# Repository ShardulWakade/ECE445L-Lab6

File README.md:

# Lab 6 Introduction to PCB Design

## Table of Contents

- [Lab 6 Introduction to PCB Design](#lab-6-introduction-to-pcb-design)
  - [Table of Contents](#table-of-contents)
  - [0 Repository Structure](#0-repository-structure)
    - [0.1 HW](#01-hw)
    - [0.2 SW](#02-sw)
    - [0.3 Resources](#03-resources)
    - [0.4 Git and Github](#04-git-and-github)
---

## 0 Repository Structure

The typical explanation for the repo structure. Lab specific instructions can be
found further below.

### 0.1 HW

The `hw` folder should contain your schematic and board files for your PCB or
circuits. In labs 1-5 and 10, you will be creating schematics for your circuit
in EAGLE. A setup tutorial can be found
[here](https://www.shawnvictor.net/autodesk-eagle.html).

### 0.2 SW

The `sw` folder should contain your application firmware and software written
for the lab. The `sw/inc` folder contains firmware drivers written for you by
Professor Valvano. Feel free to write your own (in fact, in some labs, you may
be required to write your own).

You can place any other source files in the `sw` folder. TAs will look at the
files you create and/or modify for software quality and for running your
project.

### 0.3 Resources

A couple files are provided in the Resources folder so you don't have to keep
searching for that one TI document. Some of them are immediately useful, like
the TM4C datasheet. Others may be useful for your final project, like the
TM4C_System_Design_Guidelines page.

### 0.4 Git and Github

We will extensively use Git and Github for managing lab projects. This makes it
easier for TAs to grade and help debug the project by allowing us to see commit
histories, maintain a common project structure, and likewise, it makes it easier
for students to collaborate with partners, merge different codebases, and to
debug their work by having a history of commits.

Two common ways of using Git and Github are [Github Desktop](https://desktop.github.com/) and the [command line](https://git-scm.com/downloads).
[Tutorials](https://dev.to/mollynem/git-github--workflow-fundamentals-5496) are also abundant on the net for you to peruse. We've provided a cheatsheet for git
in the Resources folder.

It is highly recommended to make the most out of Git, even if you've never used
it before. Version control will save you a lot of suffering, and tools like Git
or SVN are ubiquitous in the industry.

A gitignore file is added to the root of this repo that may prevent specific
files from being tagged to the repo. This are typically autogenerated output
files we don't care about, but sometimes other stuff (like .lib files) falls
through that we want. Feel free to modify if necessary.

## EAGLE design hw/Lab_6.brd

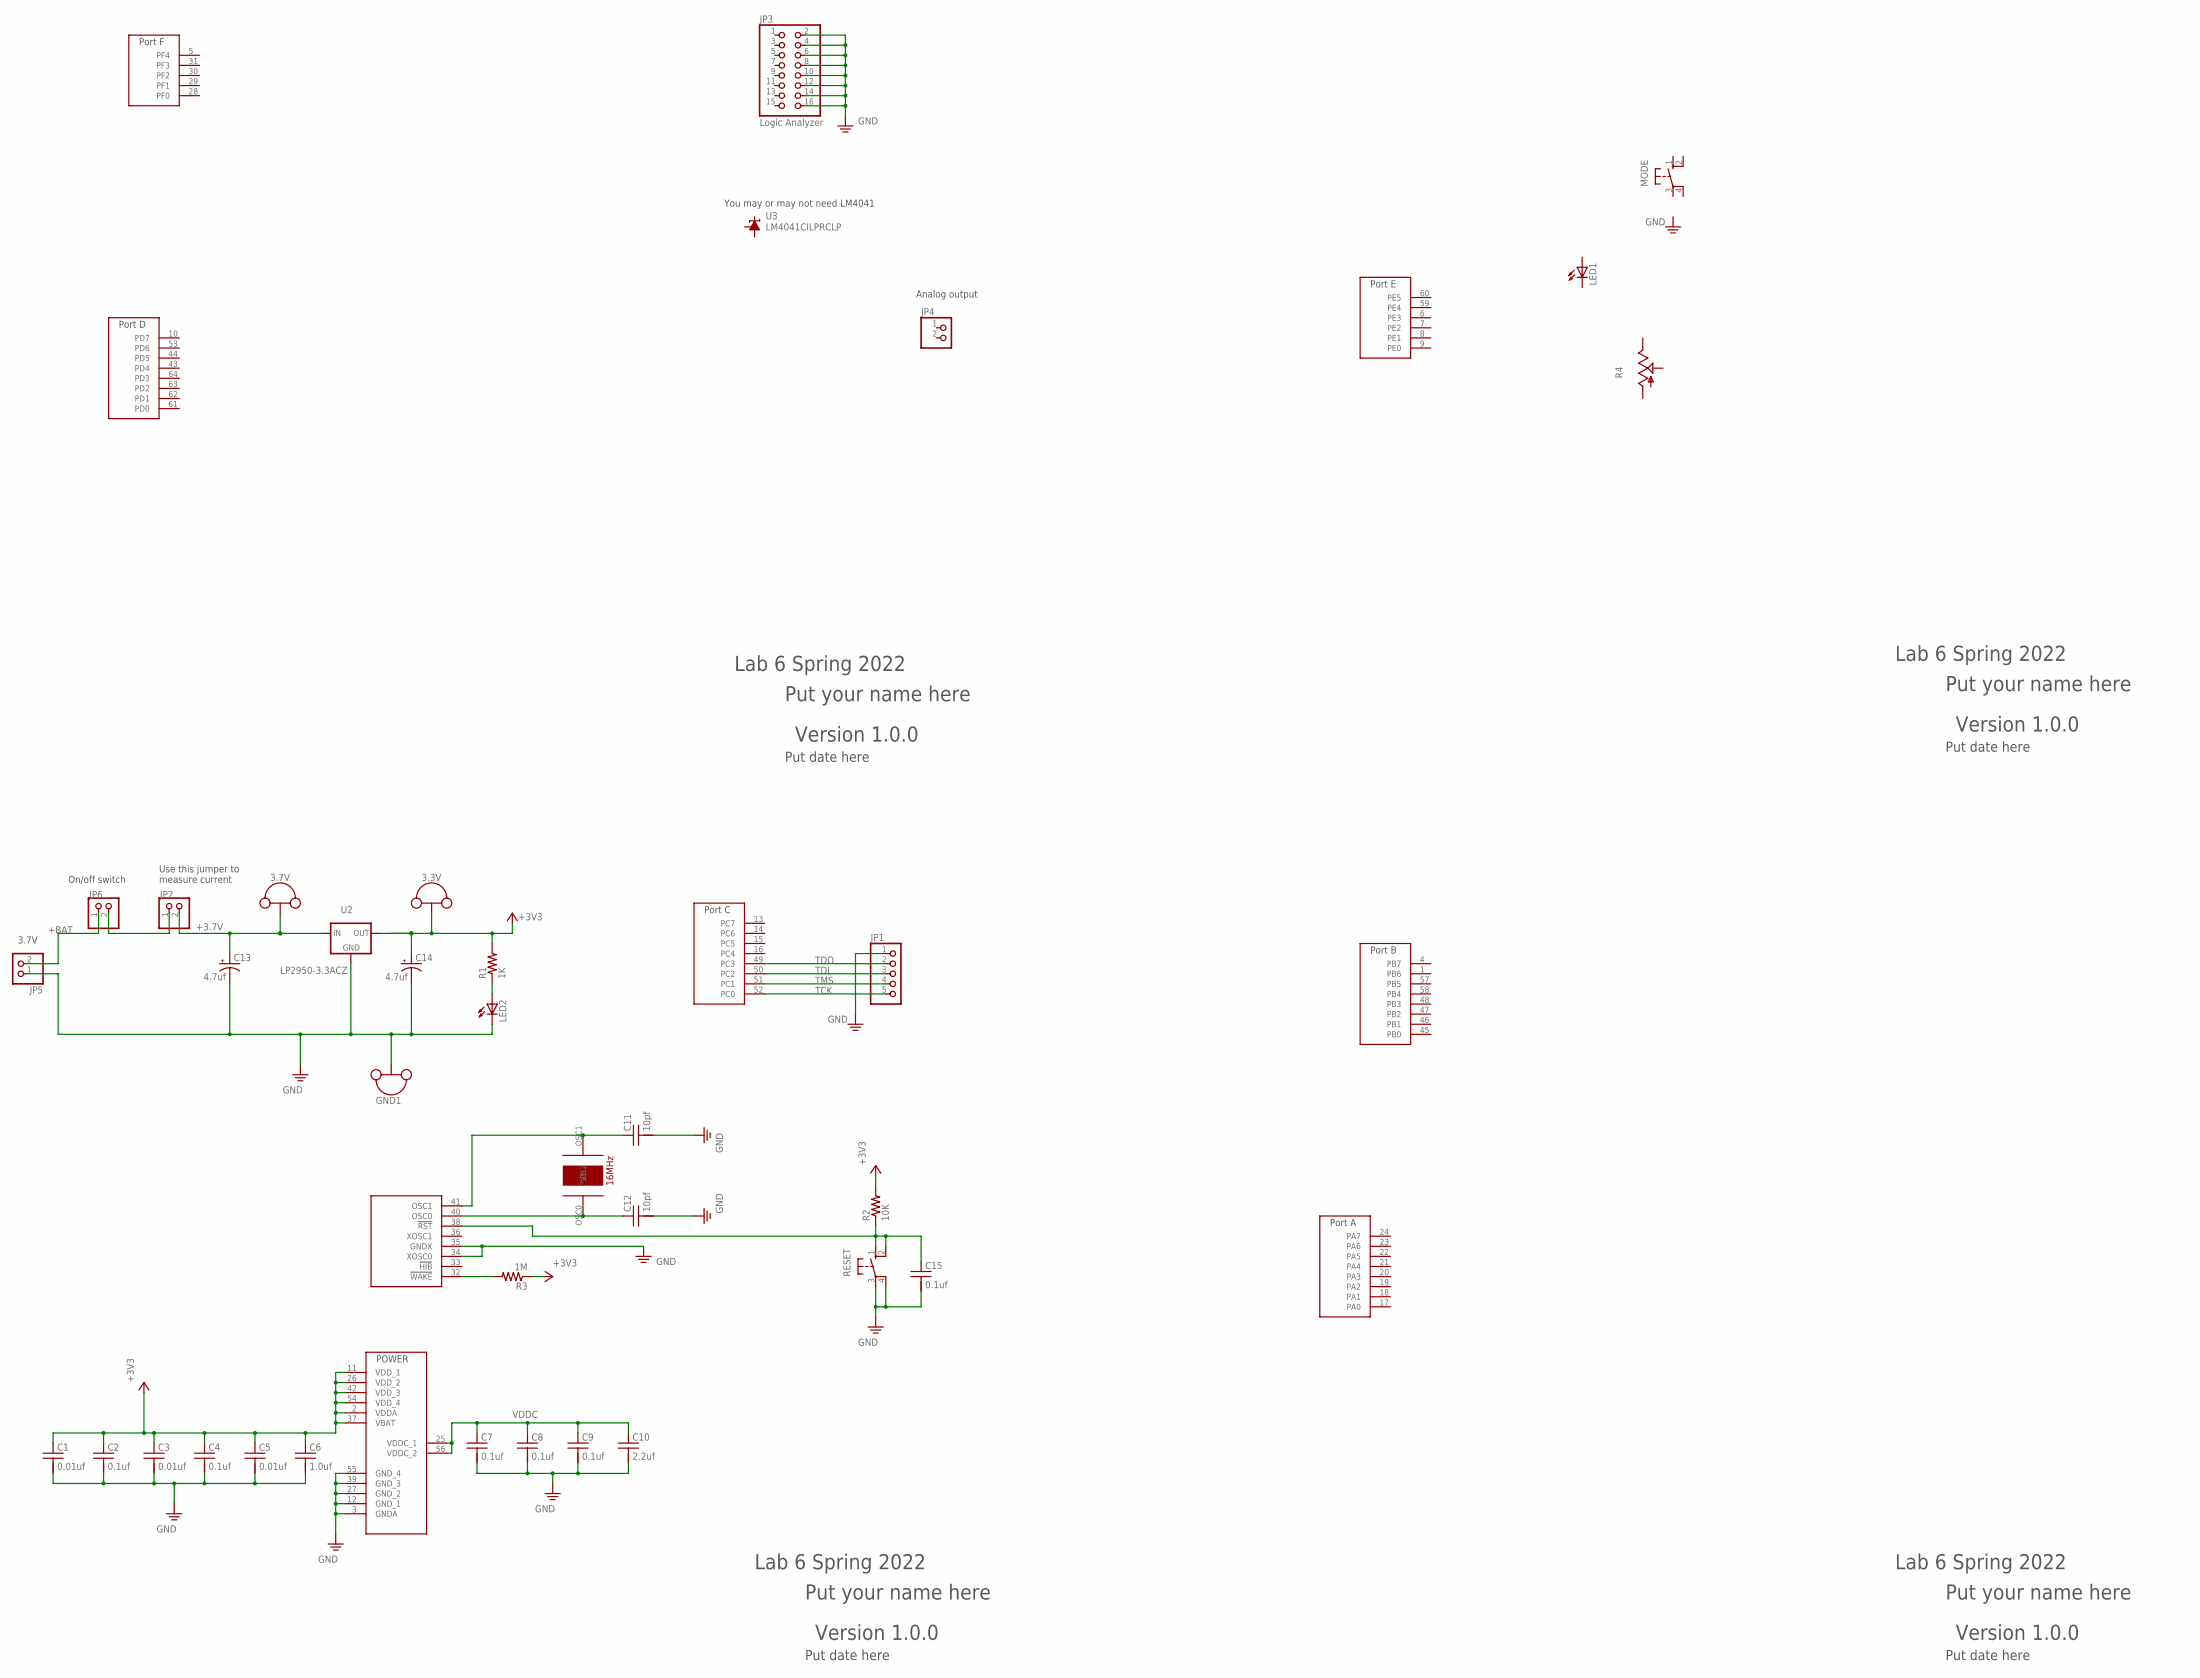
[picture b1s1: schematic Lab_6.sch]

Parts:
3.3V, 3.7V: TP_LOOP
C1, C3, C5: 0.01uf; CAP100MIL
C2, C4, C7, C8, C9, C15: 0.1uf; CAP100MIL
C6: 1.0uf; CAP100MIL
C10: 2.2uf; CAP100MIL
C11, C12: 10pf; CAP100MIL
C13, C14: 4.7uf; CAP200MILPOLARIZED
GND1: TP_LOOP
JP1: PINHD-1X5; 1X05
JP2, JP4, JP5, JP6: PINHD-1X2; 1X02
JP3: Logic Analyzer; 2X08
LED1, LED2: LED3MM
MODE: B3F-1052; B3F-10XX
R1: 1K; RES200MIL
R2: 10K; RES200MIL
R3: 1M; RES200MIL
R4: POTENTIOMETER_PTA2043B25U; PTA2043
RESET: B3F-1052; B3F-10XX
U1: TM4C123GH6PM; QFP50P1200X1200X160-64N
U2: LP2950-3.3ACZ; TO92
U3: LM4041CILPRCLP; LP_O-PBCY-W3
Y1: 16MHZ_CRYSTAL

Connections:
+3.7V: 3.7V.P$1, 3.7V.P$2, C13.+, JP2.2, U2.3 (IN)
+3V3: 3.3V.P$1, 3.3V.P$2, C1.1, C2.1, C3.1, C4.1, C5.1, C6.1, C14.+, R1.2, R2.2, R3.1, U1.2 (VDDA), U1.11 (VDD_1), U1.26 (VDD_2), U1.37 (VBAT), U1.42 (VDD_3), U1.54 (VDD_4), U2.1 (OUT)
+BAT: JP5.2, JP6.1
GND: C1.2, C2.2, C3.2, C4.2, C5.2, C6.2, C7.2, C8.2, C9.2, C10.2, C11.2, C12.2, C13.-, C14.-, C15.2, GND1.P$1, GND1.P$2, JP1.1, JP3.2, JP3.4, JP3.6, JP3.8, JP3.10, JP3.12, JP3.14, JP3.16, JP5.1, LED2.K (C), RESET.3, RESET.4 (P1), U1.3 (GNDA), U1.12 (GND_1), U1.27 (GND_2), U1.34 (XOSC0), U1.35 (GNDX), U1.39 (GND_3), U1.55 (GND_4), U2.2 (GND)
OSC0: C12.1, U1.40 (OSC0), Y1.OSC0
OSC1: C11.1, U1.41 (OSC1), Y1.OSC1
POWERLED: LED2.A, R1.1
RESET: C15.1, R2.1, RESET.1 (S), RESET.2 (S1), U1.38 (!RST)
SWITCHEDPOWER: JP2.1, JP6.2
TCK: JP1.5, U1.52 (PC0)
TDI: JP1.3, U1.50 (PC2)
TDO: JP1.2, U1.49 (PC3)
TMS: JP1.4, U1.51 (PC1)
VDDC: C7.1, C8.1, C9.1, C10.1, U1.25 (VDDC_1), U1.56 (VDDC_2)
WAKE: R3.2, U1.32 (!WAKE)

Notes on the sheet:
Use this jumper to measure current
Lab 6 Spring 2022
Put your name here
Version 1.0.0
Put date here
You may or may not need LM4041
3.7V
Analog output
On/off switch

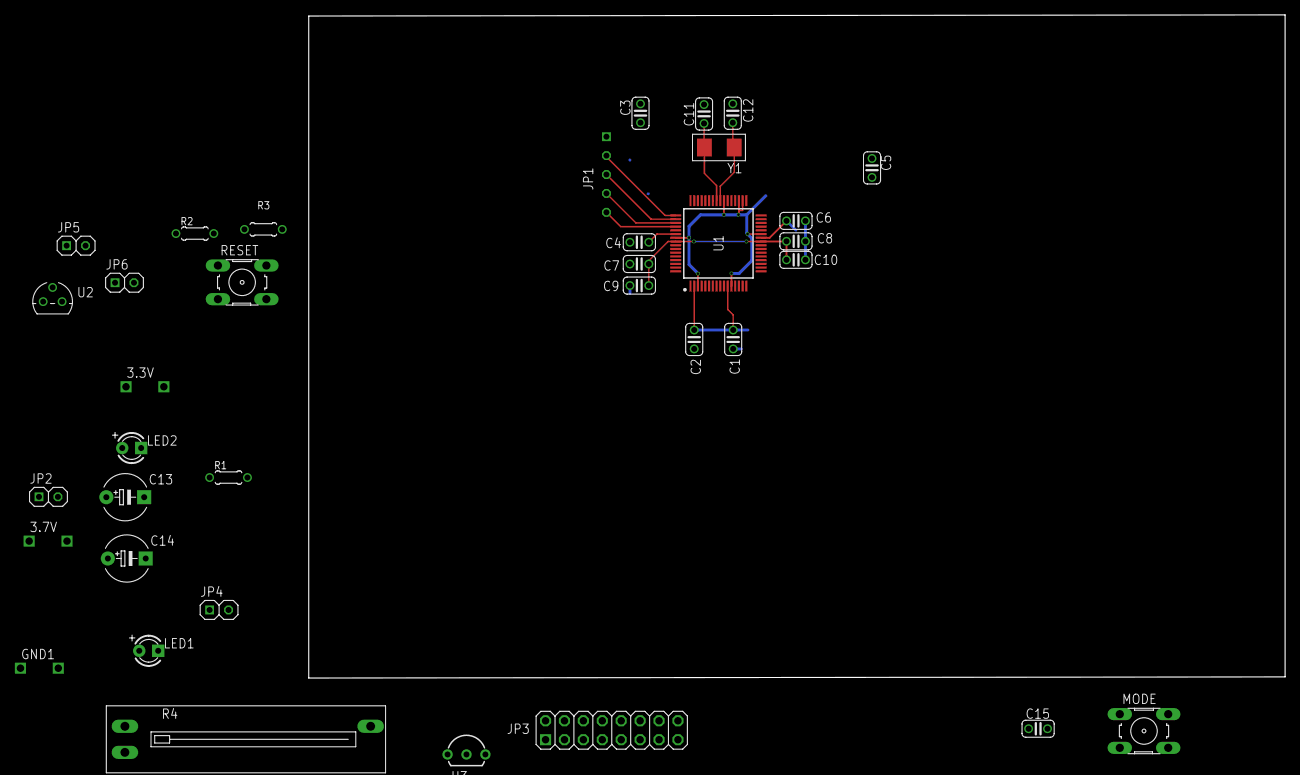
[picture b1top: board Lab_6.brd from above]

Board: 2 copper layers, 131.1 x 89.1 mm, 36 parts (1 on the bottom side), 15 nets.

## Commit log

2022-02-26 Box Resource Walkthrough
2022-02-26 Box Resources
2022-02-26 EAGLE Tips
2022-02-26 Removed Jared's personal tips and tricks
2022-02-26 change software to a md file
2022-02-26 Made the software file a read me
2022-09-30 lowercase folders and initial Lab06.md
2022-09-30 bom instructions complete
2022-09-30 add eagle bom to csv python script
2022-09-30 more edits made to Lab06 document
2022-10-04 req doc w/o pictures
2022-10-04 lab6 doc edits
2022-10-05 only have sch left
2022-10-05 final Lab06.md
2022-10-05 part datasheets
2022-10-05 final temp revisions
2022-10-05 rename Lab06.md to README.md
2022-10-05 final revisions
2022-10-09 req doc adjust
2023-10-04 rm dep files
2023-10-04 add cleared bom, new lab doc
2023-10-04 rm submodules
2023-10-19 SchematicDone
